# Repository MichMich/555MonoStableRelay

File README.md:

# 555 Mono Stable Relay

A 555 timer controlled mono stable relay designed in KiCad.

For more info check out: http://michaelteeuw.nl

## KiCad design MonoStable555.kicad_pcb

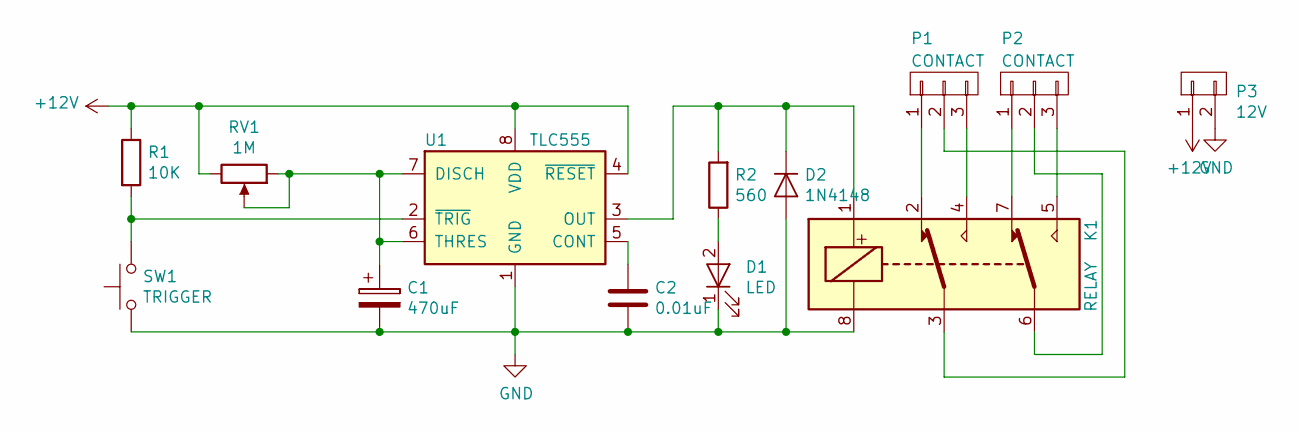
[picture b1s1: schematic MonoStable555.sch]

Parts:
C1: 470uF; CP_Radial_D6.3mm_P2.50mm
C2: 0.01uF; C_Disc_D5.0mm_W2.5mm_P2.50mm
D1: LED; LED_D3.0mm
D2: 1N4148; D_A-405_P7.62mm_Horizontal
K1: RELAY; Relay_DPDT_Omron_G5V-2
P1, P2: CONTACT; Pin_Header_Straight_1x03_Pitch2.54mm
P3: 12V; WireConnection_1.20mmDrill
R1: 10K; R_Axial_DIN0207_L6.3mm_D2.5mm_P7.62mm_Horizontal
R2: 560; R_Axial_DIN0207_L6.3mm_D2.5mm_P7.62mm_Horizontal
RV1: 1M; Potentiometer_Trimmer_ACP_CA9v_Horizontal_Px10.0mm_Py5.0mm
SW1: TRIGGER; Pin_Header_Straight_2x01_Pitch2.54mm
U1: TLC555; DIP-8_W7.62mm_Socket_LongPads

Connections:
+12V: P3.1, R1.1, RV1.3, U1.4 (~RESET), U1.8 (VDD)
GND: C1.2, C2.1, D1.1 (K), D2.2 (A), K1.8, P3.2, SW1.1, U1.1 (GND)
unnamed: C1.1, RV1.1, RV1.2, U1.6 (THRES), U1.7 (DISCH)
unnamed: C2.2, U1.5 (CONT)
unnamed: D1.2 (A), R2.1
unnamed: D2.1 (K), K1.1, R2.2, U1.3 (OUT)
unnamed: K1.2, P1.1
unnamed: K1.3, P1.2
unnamed: K1.4, P1.3
unnamed: K1.5, P2.3
unnamed: K1.6, P2.2
unnamed: K1.7, P2.1
unnamed: R1.2, SW1.2, U1.2 (~TRIG)

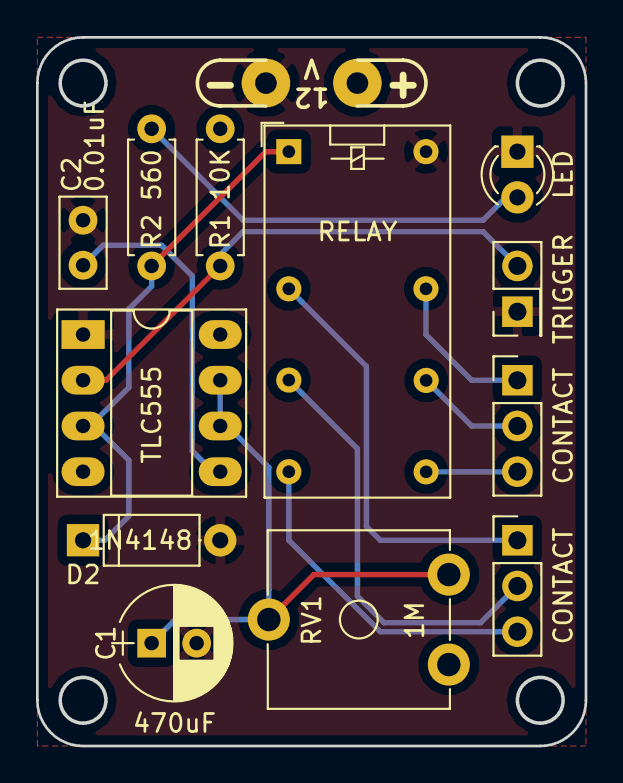
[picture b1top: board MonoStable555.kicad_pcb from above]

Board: 2 copper layers, 30.4 x 39.3 mm, 13 parts (0 on the bottom side), 13 nets.

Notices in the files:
MonoStable555.kicad_pcb:
©MIJA 1997-2017 / MICHAELTEEUW.NL
